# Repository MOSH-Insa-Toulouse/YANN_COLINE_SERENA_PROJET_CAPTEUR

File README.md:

# YANN_COLINE_SERENA_PROJET_CAPTEUR

Ce projet s'inscrit dans l'UF "*Du capteur au banc de Test*" de l'INSA Toulouse, 4ème année Génie Physique. 
Du **design** jusqu'à la **conception** en passant par le **codage**, toutes les étapes nécessaires à l'élaboration d'un capteur de déformation / jauge de contrainte à base de graphite sont détaillées dans ce dossier.

## Récapitulatif ; qu'avons-nous fait dans les grandes lignes ?

Tout d'abord, nous avons effectué nos premiers branchements et testé notre code sur notre module Arduino, contenant un amplificateur transimpédance, un écran OLED ainsi qu'un module Bluetooth. Le capteur, préalablement "colorié" avec divers types de graphite (9B, HB, 6B, ect.), permet au module d'afficher sur l'écran une résistance variable en fonction de sa déformation.
Nous avons ensuite utilisé le logiciel *MIT App Inventor* afin de réaliser une application smartphone APK, capable de lire la résistance ressentie par le capteur et de l'afficher sur un graphique à l'aide d'un module Bluetooth.
Ensuite, nous avons réalisé le design de notre shield à l'aide du logiciel *KICAD* et l'avons construit (perçage, soudage des composants, etc.) nous-même en salle de TP.
Enfin, nous avons pu effectuer différents tests sur ce nouveau PCB et caractériser la résistance du capteur en fonction de sa déformation.

## Sommaire 

* [Protocole d'utilisation du capteur de contrainte](#PremiereSection) 
* [Code Arduino](#DeuxiemeSection)
* [Application smartphone APK](#TroisiemeSection)
* [Fabrication du shield](#QuatriemeSection)
  * [Composants designés : empreintes](#QuatriemeSection1)
  * [Schématique](#QuatriemeSection2)
  * [Placement des composants](#QuatriemeSection3)
  * [Visualisation 3D](#QuatriemeSection4)
  * [Réalisation du PCB](#QuatriemeSection5)
  * [Perçage et soudure](#QuatriemeSection6)
* [Banc de test](#SixiemeSection)
  * [Résultats obtenus](#SixiemeSection1)
  * [Pistes d'améliorations](#SixiemeSection2)
* [Datasheet](#CinquiemeSection)

## Protocole d'utilisation du capteur de contrainte 

Tout d'abord, il faut brancher le module Arduino au port USB d'un ordinateur afin de le mettre sous tension. Le module Bluetooth devrait afficher un voyant rouge, clignotant à une fréquence assez rapide.

Pour commencer, il faut télécharger l'application *"MIT AI2 Companion"*. 
Ensuite, pour télécharger l'application que nous avons codée, il suffit de cliquer sur "scan QR Code" après ouverture de cette première application et de scanner le QR Code suivant : *mettre le QR Code de téléchargement*.

Une fois notre application **Projet_Capteur** téléchargée, l'interface vue est la suivante : 

Voilà la procédure à suivre afin de commencer à relever les valeurs de la résistance du capteur :

* Cliquer sur **Appareils visibles**, en haut à gauche de l'écran
* Sélectionner le module Bluetooth suivant : 
> 98:D3:51:FE:21:CD: HC-05 
(une fois la connexion établie, le voyant du Bluetooth doit clignoter de manière moins fréquente)
* Cliquer sur le bouton **ON** pour commencer à acquérir des valeurs
* A tout moment, cliquez sur **OFF** pour stopper l'acquisition.

## Code Arduino 

Le code arduino permet : 

* De récupérer la valeur de tension renvoyée par le capteur de graphène

* De l'afficher sur un écran OLED 

* D'assurer la connexion bluetooth entre le module Arduino et l'application smartphone APK

## Application smartphone APK 

Grâce au logiciel *MIT App Inventor*, nous avons pu coder une application très simple, permettant d'afficher les tension et résistance délivrées par le capteur, une fois la résistance convertie. Ensuite, cette dernière est affichée sur un graphique. Elle permet aussi d'assurer la connexion bluetooth entre le module Arduino et notre capteur.
(Pour voir comment connecter le module bluetooth à l'application, se référer à la partie _Protocole d'utilisation du capteur de contrainte_). 
L'application est codée de telle sorte à correspondre au code Arduino, afin que les valeurs que le code et l'application s'envoient mutuellement (via le module Bluetooth) corrèlent. 
En appuyant sur **ON**, l'acquisition démarre et le graphique correspondant à la valeur de la résistance mesurée par le capteur commence à se tracer. A tout moment, il est possible d'appuyer sur **OFF** pour stopper l'acquisition.

## Fabrication du PCB shield 

Pour fabriquer notre PCB shield, nous avons d'abord dû le designer à l'aide du logiciel *KICAD*. 
Le PCB sera par la suite branché sur un microcontrôleur Arduino Uno, du même type que celui que nous avions utilisé avec notre BreadBord. Ce PCB contient également l'amplificateur transimpédance, le module Bluetooth, et l'écran OLED.

### Composants designés : empreintes 

* **Ecranc OLED**

* **Module Bluetooth**

* **Amplificateur LT1050** (*empreinte présente par défaut dans le logiciel*)

### Schématique 

Une fois les empreintes créées, nous avons pu réaliser le Eeschema de notre shield. 
En haut à droite sont représentées les broches de la carte Arduino. Au centre du PCB, on trouve l'amplificateur transimpédance (permettant de traiter les données envoyées par le capteur, c'est-à-dire la variation de résistance), le module Bluetooth et l'écran OLED. 

### Placement des composants 

Ensuite, nous avons pu placer les composants sur notre PCB afin de les répartir au mieux et d'optimiser les branchements.

### Visualisation 3D 

### Réalisation du PCB 

Le PCB a été réalisé au sein du génie physique, avec l'aide de Catherine Crouzet. Le PCB est réalisé sur une plaque d'epoxy possédant une fine couche de cuivre (environ 60µm).
La silouhette du PCB (pris depuis KICAD) est d'abord imprimée sur du papier calque. Ensuite, le PCB est insolé aux UV pendant 5 minutes, avec la silouhette par-dessus. Puis à l'aide d'un révélateur, on retire la partie non insolée. 
La plaquette d'epoxy est ensuite déposée dans un bain de perchlorure de fer pour la gravure, pendant environ 5 minutes également. Le cuivre non protégé par la résine a été retiré, ce qui permet d'obtenir le PCB modélisé. 
Enfin, on applique de l'acétone sur la plaquette afin d'ôter les dernières traces de résine résiduelle.

### Perçage et soudure 

Nous avons ensuite percé notre PCB aux endroits où des composants devaient être insérés. Le diamètre des trous est de 0.8mm pour l'AOP et autres composants (résistances et capacités) et de 1mm pour les connecteurs de l'Arduino et des headers des différents modules (bluetooth, oled, etc).

## Banc de test 

Pour réaliser notre banc de test, nous avons utilisé le banc de test fourni par le Génie Physique : 7 demi-cercles en plastique, dont les diamètres varient de 1 cm à 2,5cm.

Pour différentes dureté de graphite (9B, 6B, 2H, etc), et donc pour différents capteurs, nous avons appuyé le capteur de graphène sur chacun des demi-cercles (afin qu'il en épouse la forme). Chaque rayon est donc associé à une déformation maximale applicable au capteur. Ensuite, dans les différents cas, nous avons relevé les valeurs de résistances affichées par l'application smartphone APK.

La déformation pouvant être réalisée en tension ou en compression, nous avons choisi de travailler sur une déformation en tension (le capteur est posé de telle sorte à ce que le graphène ne soit pas en contact avec le demi-cercle). 

### Résultats obtenus 

Dans tous les cas, on peut noter que quand la déflection du capteur augmente, la variation relative de résistance augmente elle aussi. Cela parait cohérent avec notre capteur ; en effet, plus le capteur est déformé, plus les atomes de carbone qui le constituent sont éloignés les uns des autres. Ainsi, le courant trouve moins facilement son chemin dans le capteur, et cela implque une augmentation de la résistance. 

### Sources d'erreurs et pistes d'améliorations 

Pour le graphène 6B, le premier point semble un peu aberrant ; plusieurs facteurs peuvent expliquer cela. 

1. Malgré une même dureté appliquée sur certains capteurs, les résultats observés variaient beaucoup ; chaque capteur, en fonction de la quantité de graphène appliquée (qui n'est jamais exactement la même), était unique. Cela ne facilitait donc pas la fiabilité des résultats.
2. Le banc de test utilisé était légèrement destructif pour le capteur. Un fois les 7 mesures effectuées, le capteur ne pouvait plus être utilisé correctement, c'est-à-dire qu'il ne pouvait pas afficher deux fois les mêmes valeurs. En considérant que l'on est capable d'appliquer exactement la même quantité de graphène sur chaque capteurs, nous pourrions envisager un protocole de mesure dans lequel nous utilisons une unique fois un capteur pour chaque mesure de résistance afin de venir supprimer ce défaut "destructif".
3. La variation de résistance n'est pas proportionnelle au type de crayon utilisé pour réaliser le capteur ; en effet, on pourrait s'attendre à ce que la variation de résistance devienne de plus en plus importante à mesure que la dureté du graphène augmente. Néanmoins, ça n'est pas le cas ici. Encore une fois, cela peut être dû à un effet rebond de la cause numéro 1 (nous n'avons pas appliqué exactement la même quantité de graphène sur chacun des capteurs). Il serait intéressant de tracer plusieurs fois la courbe de variation en fonction de la déformation d'un même type de crayon, mais en utilisant des quantité de graphène différentes sur chaque capteur. Ainsi, il serait possible de réaliser une moyenne des courbes, ce qui limiterait les erreurs dues aux variations des quantités de graphène utilisées d'un capteur à l'autre.

## Datasheet 

--> La datasheet est disponible [ici](https://github.com/MOSH-Insa-Toulouse/YANN_COLINE_SERENA_PROJET_CAPTEUR/blob/main/Datasheet_projet_capteur.pdf)

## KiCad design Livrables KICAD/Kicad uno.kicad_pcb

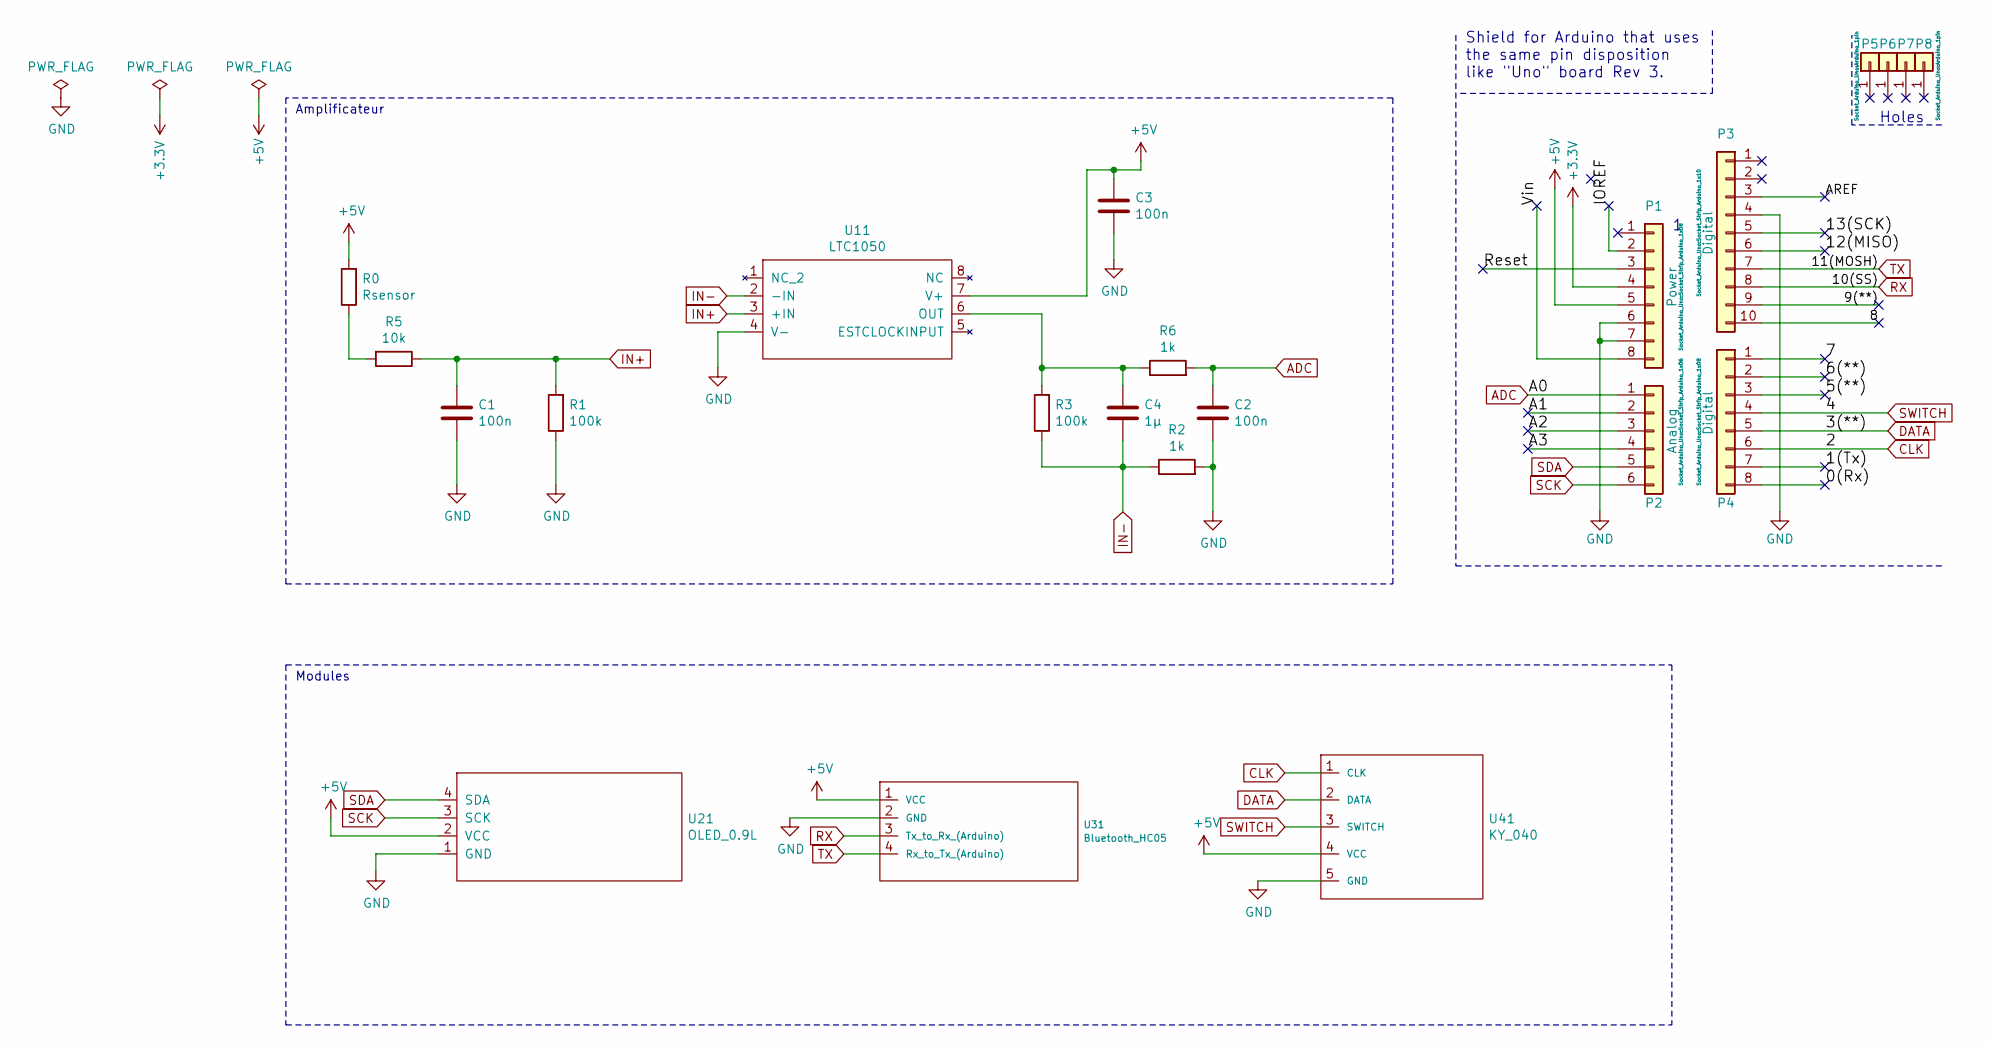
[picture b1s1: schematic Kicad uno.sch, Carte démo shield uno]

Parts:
C1, C2, C3: 100n; C_Disc_D5.1mm_W3.2mm_P5.00mm
C4: 1µ; C_Rect_L7.0mm_W4.5mm_P5.00mm
P1: Power; Socket_Strip_Arduino_1x08
P2: Analog; Socket_Strip_Arduino_1x06
P3: Digital; Socket_Strip_Arduino_1x10
P4: Digital; Socket_Strip_Arduino_1x08
P5, P6, P7, P8: CONN_01X01; Arduino_1pin
R0: Rsensor; R_Axial_DIN0204_L3.6mm_D1.6mm_P5.08mm_Horizontal
R1, R3: 100k; R_Axial_DIN0204_L3.6mm_D1.6mm_P5.08mm_Horizontal
R2, R6: 1k; R_Axial_DIN0204_L3.6mm_D1.6mm_P5.08mm_Horizontal
R5: 10k; R_Axial_DIN0204_L3.6mm_D1.6mm_P5.08mm_Horizontal
U11: LTC1050
U21: OLED_0.9L
U31: Bluetooth_HC05
U41: KY_040

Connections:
+3V3: P1.4
+5V: C3.1, P1.5, R0.2, U11.7 (V+), U21.2 (VCC), U31.1 (VCC), U41.4 (VCC)
/0(Rx): P4.8
/1(Tx): P4.7
/5(**): P4.3
/6(**): P4.2
/7: P4.1
/8: P3.10
/9(**): P3.9
/12(MISO): P3.6
/13(SCK): P3.5
/A1: P2.2
/A2: P2.3
/A3: P2.4
/AREF: P3.3
/IOREF: P1.2
/Reset: P1.3
/Vin: P1.8
ADC: C2.1, P2.1, R6.2
CLK: P4.6, U41.1 (CLK)
DATA: P4.5, U41.2 (DATA)
GND: C1.2, C2.2, C3.2, P1.6, P1.7, P3.4, R1.1, R2.2, U11.4 (V-), U21.1 (GND), U31.2 (GND), U41.5 (GND)
IN+: C1.1, R1.2, R5.1, U11.3 (+IN)
IN-: C4.2, R2.1, R3.1, U11.2 (-IN)
unnamed: C4.1, R3.2, R6.1, U11.6 (OUT)
unnamed: R0.1, R5.2
RX: P3.8, U31.3 (Tx_to_Rx_(Arduino))
SCK: P2.6, U21.3 (SCK)
SDA: P2.5, U21.4 (SDA)
SWITCH: P4.4, U41.3 (SWITCH)
TX: P3.7, U31.4 (Rx_to_Tx_(Arduino))

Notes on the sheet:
Holes
Shield for Arduino that uses the same pin disposition like "Uno" board Rev 3.
Amplificateur
Modules

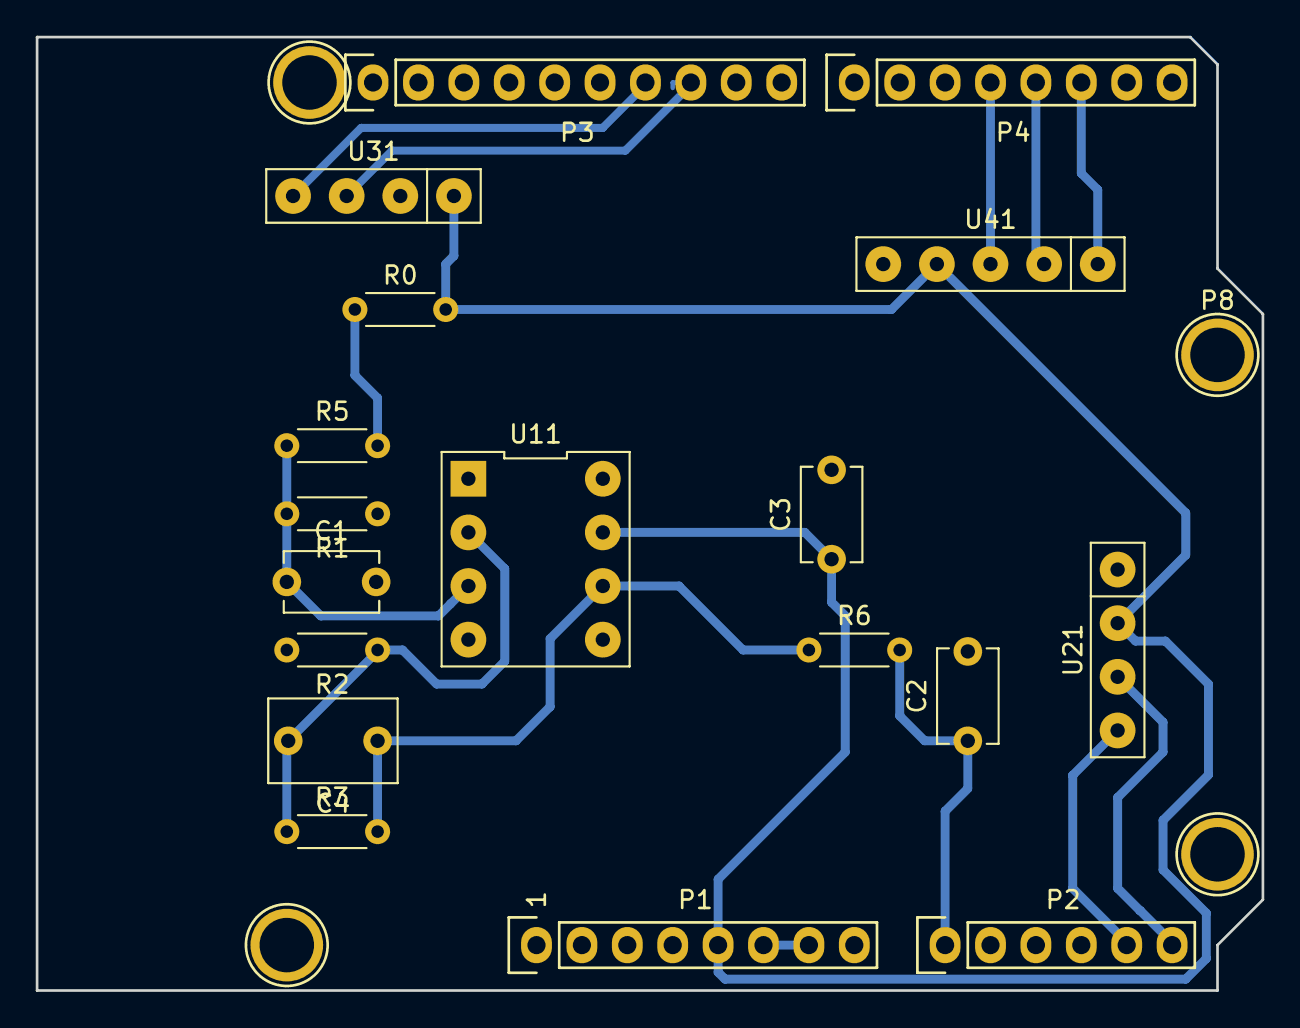
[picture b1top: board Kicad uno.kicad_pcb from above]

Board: 2 copper layers, 68.6 x 53.3 mm, 22 parts (0 on the bottom side), 14 nets.

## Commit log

2021-03-20 Update README.md
    Ajout d'informations supplémentaires concernant le déroulement du projet.
